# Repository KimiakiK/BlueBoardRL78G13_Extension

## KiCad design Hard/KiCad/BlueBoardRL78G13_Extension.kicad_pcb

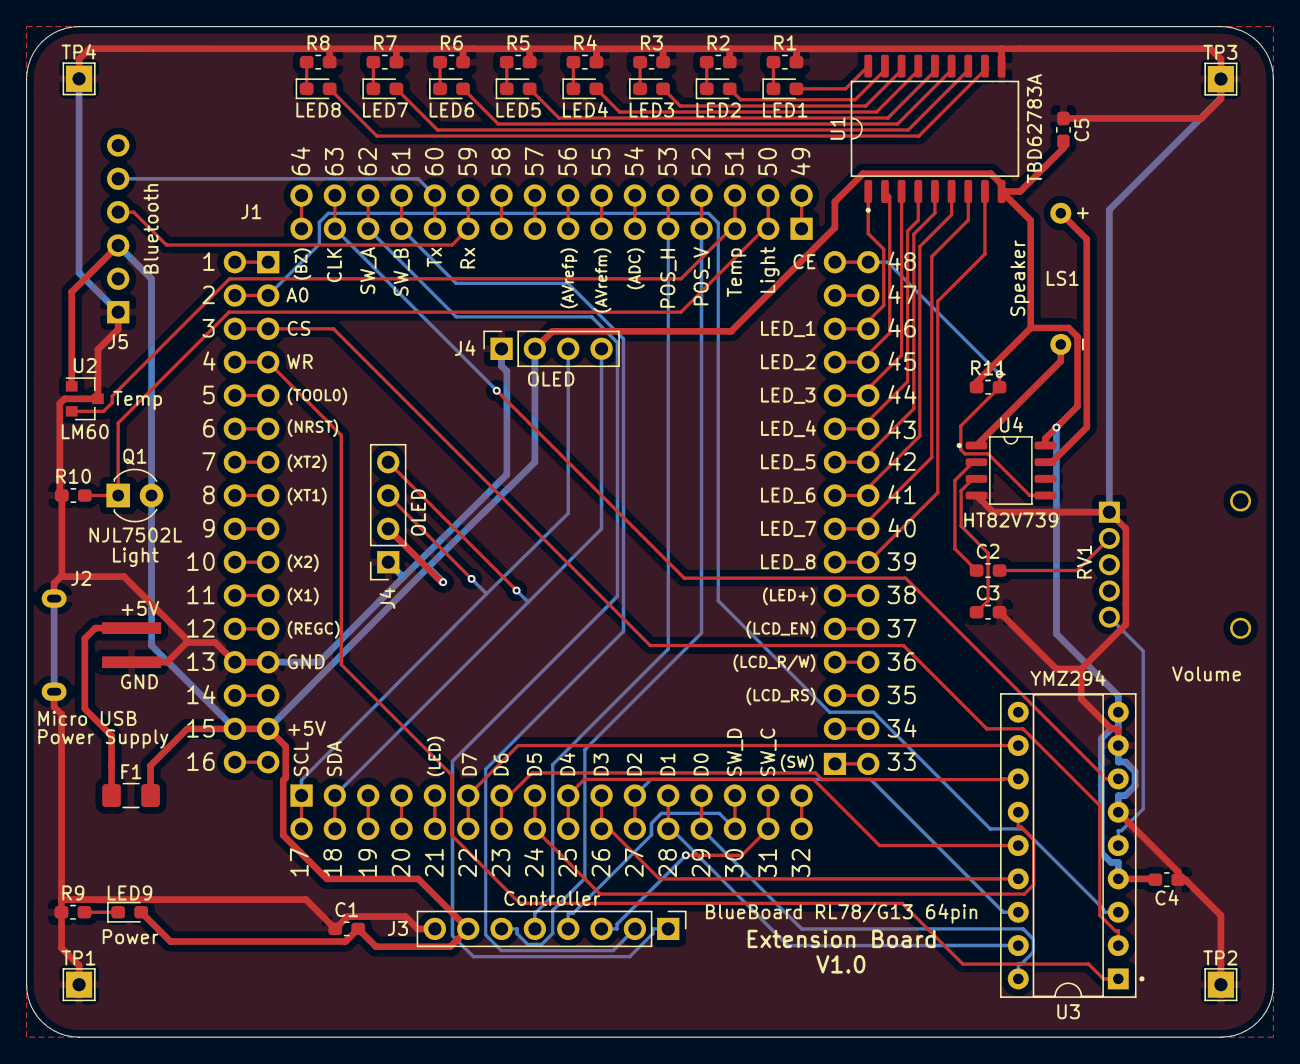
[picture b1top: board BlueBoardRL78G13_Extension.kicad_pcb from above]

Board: 2 copper layers, 95.0 x 77.0 mm, 43 parts (0 on the bottom side), 59 nets.

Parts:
C1, C4, C5: 0.1uF; C_0603_1608Metric_Pad1.05x0.95mm_HandSolder
C2, C3: 1uF; C_0603_1608Metric_Pad1.05x0.95mm_HandSolder
F1: MF-NSMF035X; Fuse_1206_3216Metric_Pad1.42x1.75mm_HandSolder
J1: RL78G13_64pin_Connector
J2: USB_B_Micro; USB_Micro-B_PowerOnly
J3: Controller; PinHeader_1x08_P2.54mm_Vertical
J4, J4#2: OLED; PinSocket_1x04_P2.54mm_Vertical
J5: AE-RN4020-XB; PinSocket_1x06_P2.54mm_Vertical
LED1: LED1; LED_0603_1608Metric_Pad1.05x0.95mm_HandSolder
LED2: LED2; LED_0603_1608Metric_Pad1.05x0.95mm_HandSolder
LED3: LED3; LED_0603_1608Metric_Pad1.05x0.95mm_HandSolder
LED4: LED4; LED_0603_1608Metric_Pad1.05x0.95mm_HandSolder
LED5: LED5; LED_0603_1608Metric_Pad1.05x0.95mm_HandSolder
LED6: LED6; LED_0603_1608Metric_Pad1.05x0.95mm_HandSolder
LED7: LED7; LED_0603_1608Metric_Pad1.05x0.95mm_HandSolder
LED8: LED8; LED_0603_1608Metric_Pad1.05x0.95mm_HandSolder
LED9: Power; LED_0603_1608Metric_Pad1.05x0.95mm_HandSolder
LS1: Speaker; Speaker_MSI28-12R
Q1: NJL7502L
R1, R2, R3, R4, R5, R6, R7, R8, R9: 1k; R_0603_1608Metric_Pad1.05x0.95mm_HandSolder
R10, R11: 10k; R_0603_1608Metric_Pad1.05x0.95mm_HandSolder
RV1: 10k; Volume_RK10J
TP1, TP2, TP3, TP4: TestPoint; TestPoint_THTPad_2.0x2.0mm_Drill1.0mm
U1: TBD62783A; SOP-18_7x12.5mm_P1.27mm
U2: LM60; SOT-23
U3: YMZ294; DIP-18_W7.62mm_Socket
U4: HT82V739; SOP-8_3.9x4.9mm_P1.27mm

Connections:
+5V: C1.2, C4.2, C5.2, F1.1, J1.15, J3.7, J4.2, J4#2.2, J5.3, LED9.2, Q1.1, R11.1, U1.9, U2.1, U3.4, U3.9, U4.8
/SP+: LS1.2, U4.7
/SP-: LS1.1, U4.1
/Sound: RV1.3, U3.5
AMP_CE: J1.48, R11.2, U4.5
BT_RX: J1.59, J5.4
BT_TX: J1.60, J5.5
GND: C1.1, C3.2, C4.1, C5.1, J1.13, J2.5, J2.6, J3.8, J4.1, J4#2.1, J5.1, R1.2, R2.2, R3.2, R4.2, R5.2, R6.2, R7.2, R8.2, R9.1, R10.1, RV1.1, TP1.1, TP2.1, TP3.1, TP4.1, U1.10, U2.3, U3.6, U3.8, U4.4
LED_1: J1.46, U1.1
LED_2: J1.45, U1.2
LED_3: J1.44, U1.3
LED_4: J1.43, U1.4
LED_5: J1.42, U1.5
LED_6: J1.41, U1.6
LED_7: J1.40, U1.7
LED_8: J1.39, U1.8
Light: J1.50, Q1.2, R10.2
unnamed: C2.1, U4.2
unnamed: C2.2, RV1.2
unnamed: C3.1, U4.3
unnamed: F1.2, J2.1
unnamed: LED1.1, R1.1
unnamed: LED1.2, U1.18
unnamed: LED2.1, R2.1
unnamed: LED2.2, U1.17
unnamed: LED3.1, R3.1
unnamed: LED3.2, U1.16
unnamed: LED4.1, R4.1
unnamed: LED4.2, U1.15
unnamed: LED5.1, R5.1
unnamed: LED5.2, U1.14
unnamed: LED6.1, R6.1
unnamed: LED6.2, U1.13
unnamed: LED7.1, R7.1
unnamed: LED7.2, U1.12
unnamed: LED8.1, R8.1
unnamed: LED8.2, U1.11
unnamed: LED9.1, R9.2
OLED_SCL: J1.17, J4.3, J4#2.3
OLED_SDA: J1.18, J4.4, J4#2.4
POS_H: J1.53, J3.5
POS_V: J1.52, J3.6
SW_A: J1.62, J3.1
SW_B: J1.61, J3.2
SW_C: J1.31, J3.3
SW_D: J1.30, J3.4
Temp: J1.51, U2.2
YMZ294_A0: J1.2, U3.3
YMZ294_CLK: J1.63, U3.7
YMZ294_CS: J1.3, U3.2
YMZ294_D0: J1.29, U3.18
YMZ294_D1: J1.28, U3.17
YMZ294_D2: J1.27, U3.16
YMZ294_D3: J1.26, U3.15
YMZ294_D4: J1.25, U3.14
YMZ294_D5: J1.24, U3.13
YMZ294_D6: J1.23, U3.12
YMZ294_D7: J1.22, U3.11
YMZ294_WR: J1.4, U3.1

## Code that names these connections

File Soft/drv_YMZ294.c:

/*
 * drv_YMZ294.c
 *
 *  Created on: May 2, 2020
 *      Author: kimi
 */

/********** Include **********/

#include "main.h"
#include "drv_YMZ294.h"
#include "drv_YMZ294_rodata.h"

/********** Define **********/

#define MAIN_PERIOD	(10)	/* メイン周期[ms] */

enum job_state_enum {
	JOB_STATE_STOP = 0,
	JOB_STATE_PLAYING,
	JOB_STATE_END
};

/********** Type **********/

typedef struct job_type {
	uint8_t type;
	uint8_t state;
	note_t* music;
	uint16_t note_num;
	uint16_t note_index;
	uint16_t note_timer;
	uint8_t volume;
} job_t;

/********** Constant **********/

/********** Variable **********/

static job_t job[YMZ294_CH_NUM];

/********** Function Prototype **********/

static void initJob(uint8_t channel);
static void writeRegister(uint8_t addr, uint8_t data);
static void outputDataPin(uint8_t data);

/********** Function **********/

/*=== 初期化関数 ===*/
void DrvYMZ294Init(void)
{
	uint8_t channel;

	/* ジョブ初期化 */
	for (channel=0; channel<YMZ294_CH_NUM; channel++) {
		initJob(channel);
	}

	// YMZ294のレジスタを全て初期化
	// ミキサーOFF
	writeRegister(YMZ294_ADDR_MIXER, 0x3F);

	// 音量0
	writeRegister(YMZ294_ADDR_VOLUME + YMZ294_CH_A, YMZ294_VOLUME_MUTE);
	writeRegister(YMZ294_ADDR_VOLUME + YMZ294_CH_B, YMZ294_VOLUME_MUTE);
	writeRegister(YMZ294_ADDR_VOLUME + YMZ294_CH_C, YMZ294_VOLUME_MUTE);

	// 楽音周波数初期化
	writeRegister(YMZ294_ADDR_FREQ + YMZ294_ADDR_L + YMZ294_CH_A, 0x00);
	writeRegister(YMZ294_ADDR_FREQ + YMZ294_ADDR_H + YMZ294_CH_A, 0x00);
	writeRegister(YMZ294_ADDR_FREQ + YMZ294_ADDR_L + YMZ294_CH_B, 0x00);
	writeRegister(YMZ294_ADDR_FREQ + YMZ294_ADDR_H + YMZ294_CH_B, 0x00);
	writeRegister(YMZ294_ADDR_FREQ + YMZ294_ADDR_L + YMZ294_CH_C, 0x00);
	writeRegister(YMZ294_ADDR_FREQ + YMZ294_ADDR_H + YMZ294_CH_C, 0x00);

	// ノイズ音周波数初期化
	writeRegister(YMZ294_ADDR_NOISE, 0x00);

	// エンベロープ周波数初期化
	writeRegister(YMZ294_ADDR_ENVE_FREQ + YMZ294_ADDR_L, 0x00);
	writeRegister(YMZ294_ADDR_ENVE_FREQ + YMZ294_ADDR_H, 0x00);

	// エンベロープ形状初期化
	writeRegister(YMZ294_ADDR_ENVE_TYPE, 0x00);


	// ミキサー チャネルA,B,C出力許可
	writeRegister(YMZ294_ADDR_MIXER, 0x38);
}

/*=== 周期関数 ===*/
void DrvYMZ294Main(void)
{
	uint8_t channel;

	for (channel=0; channel<YMZ294_CH_NUM; channel++) {
		switch (job[channel].state) {
		case JOB_STATE_STOP:
			/* 処理なし */
			break;
		case JOB_STATE_PLAYING:
			job[channel].note_timer += MAIN_PERIOD;
			if (job[channel].note_timer == MAIN_PERIOD) {
				/* 音開始 */
				if ((job[channel].music + job[channel].note_index)->pitch != NOTE_REST) {
					DrvYMZ294SetFrequency(channel, (job[channel].music + job[channel].note_index)->pitch);
					job[channel].volume = YMZ294_VOLUME_MAX;
					DrvYMZ294SetVolume(channel, job[channel].volume);
				} else {
					job[channel].volume = YMZ294_VOLUME_MUTE;
					DrvYMZ294SetVolume(channel, job[channel].volume);
				}
			} else if (job[channel].note_timer > (job[channel].music + job[channel].note_index)->duration) {
				/* 音終了 */
				job[channel].note_timer = 0;
				job[channel].note_index++;
				if (job[channel].note_index >= job[channel].note_num) {
					job[channel].state = JOB_STATE_END;
				}
			} else {
				/* 音出力中 */
				if ((job[channel].music + job[channel].note_index)->pitch != NOTE_REST) {
					uint8_t progress;
					uint8_t volume;
					progress = job[channel].note_timer / ((job[channel].music + job[channel].note_index)->duration / 10);
					if (progress <= 5) {
						volume = YMZ294_VOLUME_MAX;
					} else if (progress <= 6) {
						volume = YMZ294_VOLUME_MAX / 2;
					} else if (progress <= 8) {
						volume = YMZ294_VOLUME_MAX / 4;
					} else {
						volume = YMZ294_VOLUME_MAX / 8;
					}
					if (job[channel].volume != volume) {
						job[channel].volume = volume;
						DrvYMZ294SetVolume(channel, job[channel].volume);
					}
				}
			}
			break;
		case JOB_STATE_END:
			if (job[channel].type == JOB_TYPE_ONCE) {
				initJob(channel);
				job[channel].volume = YMZ294_VOLUME_MUTE;
				DrvYMZ294SetVolume(channel, job[channel].volume);
			} else {
				job[channel].state = JOB_STATE_PLAYING;
				job[channel].note_index = 0;
				job[channel].note_timer = 0;
			}
			break;
		default:
			initJob(channel);
			break;
		}
	}
}

/*=== ジョブ設定関数 ===*/
void DrvYMZ294SetJob(uint8_t channel, music_t* music, uint8_t job_type)
{
	if (channel < YMZ294_CH_NUM) {
		initJob(channel);
		job[channel].type = job_type;
		job[channel].music = music->note_address;
		job[channel].note_num = music->note_num;
		job[channel].state = JOB_STATE_PLAYING;
	}
}

/*=== 音量設定関数 ===*/
void DrvYMZ294SetVolume(uint8_t channel, uint8_t volume)
{
	if ((channel < YMZ294_CH_NUM) && (volume <= YMZ294_VOLUME_MAX)){
		writeRegister(YMZ294_ADDR_VOLUME + channel, volume);
	}
}

/*=== 周波数設定関数 ===*/
void DrvYMZ294SetFrequency(uint8_t channel, uint8_t freq_table_index)
{
	if ((channel < YMZ294_CH_NUM) && (freq_table_index >= YMZ294_FREQ_TABLE_MIN) && (freq_table_index < YMZ294_FREQ_TABLE_MAX)){
		writeRegister(YMZ294_ADDR_FREQ + YMZ294_ADDR_L + channel * 2, YMZ294_Freq_Table_L[freq_table_index]);
		writeRegister(YMZ294_ADDR_FREQ + YMZ294_ADDR_H + channel * 2, YMZ294_Freq_Table_H[freq_table_index]);
	}
}

/*=== ジョブ初期化関数 ===*/
static void initJob(uint8_t channel)
{
	job[channel].type = JOB_TYPE_ONCE;
	job[channel].state = JOB_STATE_STOP;
	job[channel].music = (void *)0;
	job[channel].note_num = 0;
	job[channel].note_index = 0;
	job[channel].note_timer = 0;
	job[channel].volume = YMZ294_VOLUME_MUTE;
}

static void writeRegister(uint8_t addr, uint8_t data)
{
	// アドレス書き込み
	HAL_GPIO_WritePin(YMZ294_A0_GPIO_Port, YMZ294_A0_Pin, GPIO_PIN_RESET);
	// 書き込み開始
	HAL_GPIO_WritePin(YMZ294_CS_GPIO_Port, YMZ294_CS_Pin, GPIO_PIN_RESET);
	// アドレス値設定
	outputDataPin(addr);
	// 書き込み終了
	HAL_GPIO_WritePin(YMZ294_CS_GPIO_Port, YMZ294_CS_Pin, GPIO_PIN_SET);

	// データ書き込み
	HAL_GPIO_WritePin(YMZ294_A0_GPIO_Port, YMZ294_A0_Pin, GPIO_PIN_SET);
	// 書き込み開始
	HAL_GPIO_WritePin(YMZ294_CS_GPIO_Port, YMZ294_CS_Pin, GPIO_PIN_RESET);
	// データ値設定
	outputDataPin(data);
	// 書き込み終了
	HAL_GPIO_WritePin(YMZ294_CS_GPIO_Port, YMZ294_CS_Pin, GPIO_PIN_SET);
}

static void outputDataPin(uint8_t data)
{
	if ((data & 0x01) == 0x01) {
		HAL_GPIO_WritePin(YMZ294_D0_GPIO_Port, YMZ294_D0_Pin, GPIO_PIN_SET);
	} else {
		HAL_GPIO_WritePin(YMZ294_D0_GPIO_Port, YMZ294_D0_Pin, GPIO_PIN_RESET);
	}
	if ((data & 0x02) == 0x02) {
		HAL_GPIO_WritePin(YMZ294_D1_GPIO_Port, YMZ294_D1_Pin, GPIO_PIN_SET);
	} else {
		HAL_GPIO_WritePin(YMZ294_D1_GPIO_Port, YMZ294_D1_Pin, GPIO_PIN_RESET);
	}
	if ((data & 0x04) == 0x04) {
		HAL_GPIO_WritePin(YMZ294_D2_GPIO_Port, YMZ294_D2_Pin, GPIO_PIN_SET);
	} else {
		HAL_GPIO_WritePin(YMZ294_D2_GPIO_Port, YMZ294_D2_Pin, GPIO_PIN_RESET);
	}
	if ((data & 0x08) == 0x08) {
		HAL_GPIO_WritePin(YMZ294_D3_GPIO_Port, YMZ294_D3_Pin, GPIO_PIN_SET);
	} else {
		HAL_GPIO_WritePin(YMZ294_D3_GPIO_Port, YMZ294_D3_Pin, GPIO_PIN_RESET);
	}
	if ((data & 0x10) == 0x10) {
		HAL_GPIO_WritePin(YMZ294_D4_GPIO_Port, YMZ294_D4_Pin, GPIO_PIN_SET);
	} else {
		HAL_GPIO_WritePin(YMZ294_D4_GPIO_Port, YMZ294_D4_Pin, GPIO_PIN_RESET);
	}
	if ((data & 0x20) == 0x20) {
		HAL_GPIO_WritePin(YMZ294_D5_GPIO_Port, YMZ294_D5_Pin, GPIO_PIN_SET);
	} else {
		HAL_GPIO_WritePin(YMZ294_D5_GPIO_Port, YMZ294_D5_Pin, GPIO_PIN_RESET);
	}
	if ((data & 0x40) == 0x40) {
		HAL_GPIO_WritePin(YMZ294_D6_GPIO_Port, YMZ294_D6_Pin, GPIO_PIN_SET);
	} else {
		HAL_GPIO_WritePin(YMZ294_D6_GPIO_Port, YMZ294_D6_Pin, GPIO_PIN_RESET);
	}
	if ((data & 0x80) == 0x80) {
		HAL_GPIO_WritePin(YMZ294_D7_GPIO_Port, YMZ294_D7_Pin, GPIO_PIN_SET);
	} else {
		HAL_GPIO_WritePin(YMZ294_D7_GPIO_Port, YMZ294_D7_Pin, GPIO_PIN_RESET);
	}
}

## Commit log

2020-09-26 Add hardware documents
2020-09-27 Add YMZ294 Driver
2020-09-29 Update YMZ294 Driver
2020-10-01 Fixed YMZ294 Driver
2020-10-04 Add OLED (SSD1306) Driver
